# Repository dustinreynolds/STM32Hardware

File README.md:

# STM32Hardware
Repository for Kicad board development and support libraries

This repository was created on Windows using Kicad built from source using [kicad-winbuilder3.4](https://launchpad.net/kicad-winbuilder).

## Folder Hierarchy 
* Calculations - Brief calculations performed
* kicad_lib - Libraries created for new schematic or pcb objects
* Nucleo_L152RE - contains board designs that have been designed using Kicad build on 2015-05-11 from BZR commit 5650.

## Hardware Releases
So far none of the designs in this repository have been tested and verified to be working.  Footprints have been aligned with the actual components, but until the actual PCB's and the remaining components arrive, this repository should serve as a reference only.  This readme will be updated to reflect the latest testing status.

ProtoBoard Rev AA had the following issues:
	Using 5 pins from morpheo headers that didn't have a pin on them.
	RFM69HW footprint was backwards for part of it.
	See AA schematics for additional notes.

Protoboard Rev AB made the following changes:
	Removed USB, replaced with low voltage relay and fet
	Added Crypto chip ATSHA204A to i2c bus
	Added GPS to I2C bus (those same pins can be used as USART)
	Split schematic into 5 pages to ease readability
	Added 5V in and use that as main power input signal (this leaves programmer unpowered)
	Added additional voltage sense pins on 5V connector for monitoring state of battery pack
	Added 3.3V regulator that can be controlled via enable pin.  This is so SPI/I2C/OneWire devices can be powered off easily.  On board chips have low power requirements when asleep.
	Added additional spare Gnd, 3.3V, 3.3Vctl, and 5.0V lines for expansion.
	Added Servo power input for motionsense 1 and 2 (which are also pwm pins)
	Added piezo buzzer on OneWire3
	Added CS pin for RGB connector since it can be a spare SPI
	Removed mounting holes since this is securely mounted to Nucleo board.

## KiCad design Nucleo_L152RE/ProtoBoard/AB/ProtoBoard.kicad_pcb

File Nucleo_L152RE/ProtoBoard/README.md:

# STM32L152RE

The STM32 L series offers low power sleep modes that can be easily utilized to form a network of low power sensing nodes which each have the power of a 32-bit ARM Cortex M3 processor.  This board was designed to leverage these low power modes by adding high power wireless modules with low sleep currents and an on-expansion-board 128 Mb FLASH chip for offline sensor measurements.

THe STM32L152RE has 512KB of flash, 80 KB Ram and ECC backed 16KB EEPROM.  The most compelling feature was the [OpenSTM32](OpenSTM32.org) System Workbench for STM32.  Utilizing an Eclipse base IDE, Eclipse plugins are installed which give you a relatively seamless transition from writing code to debugging it.  The debugger is OpenOCD, utilizing the ST-Link. There are growing pains when transitioning to any platform, but the performance and recent availability of high quality tools make the STM32 a hot platform to start projects on. 

Development boards for a wide range of STM32 processors can be found for under $11.  Although each of those development boards only offer 64 pin packages of each respective processor, much can be done with that core subset of pins.

# Kicad Schematics and Printed Circuit Boards

## ProtoBoard
First Kicad release for the Nucleo-L152RE development board. This development board will serve as a low power platform for performing sensor measurements around my house.  Each STM32 expansion board will contain an RFM69HW wireless transceiver and will be capable of broadcasting events to the wireless network.  A listening device will then notify the owner of the event so that rapid action can occur.

### Event Detection and Alerting
The following events will be monitored
* Water leak (toilets, AC drip pan, Water Heater)
* Room temperature
* Stove burner or oven left on
* Door/window opens or closes
* Plant moisture sensing
* Dryer temperature and timing

### Firmware
The associated firmware can be found at the [SensorNodes Project](https://github.com/dustinreynolds/SensorNodes/tree/develop).  The Git-Flow paradigm is in use, so code can be found in the develop branch until a functioning first release is released, at which point it will be in the master branch (and show up by default on Github).

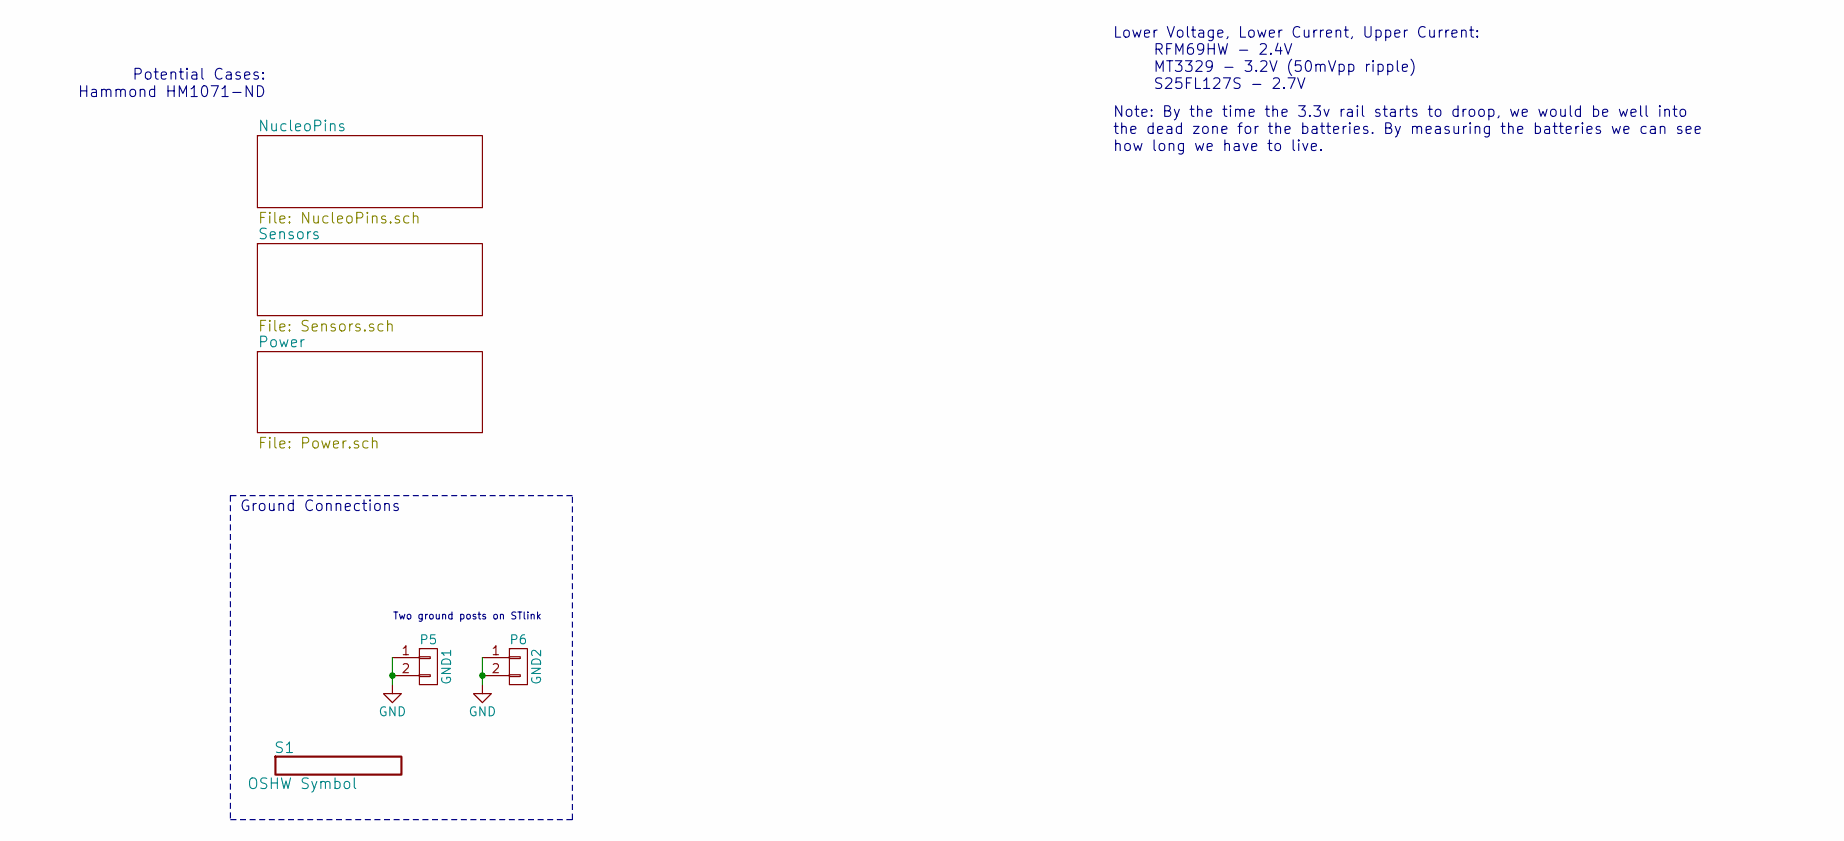
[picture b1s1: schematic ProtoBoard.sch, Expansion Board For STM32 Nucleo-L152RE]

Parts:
P5: GND1; Pin_Header_Straight_1x02
P6: GND2; Pin_Header_Straight_1x02
S1: OSHW Symbol; Symbol_OSHW-Logo_SilkScreen

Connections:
GND: P5.1, P5.2, P6.1, P6.2; also elsewhere on the board

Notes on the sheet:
Potential Cases: Hammond HM1071-ND
Ground Connections
Two ground posts on STlink
Lower Voltage, Lower Current, Upper Current: RFM69HW - 2.4V MT3329 - 3.2V (50mVpp ripple) S25FL127S - 2.7V
Note: By the time the 3.3v rail starts to droop, we would be well into the dead zone for the batteries. By measuring the batteries we can see how long we have to live.

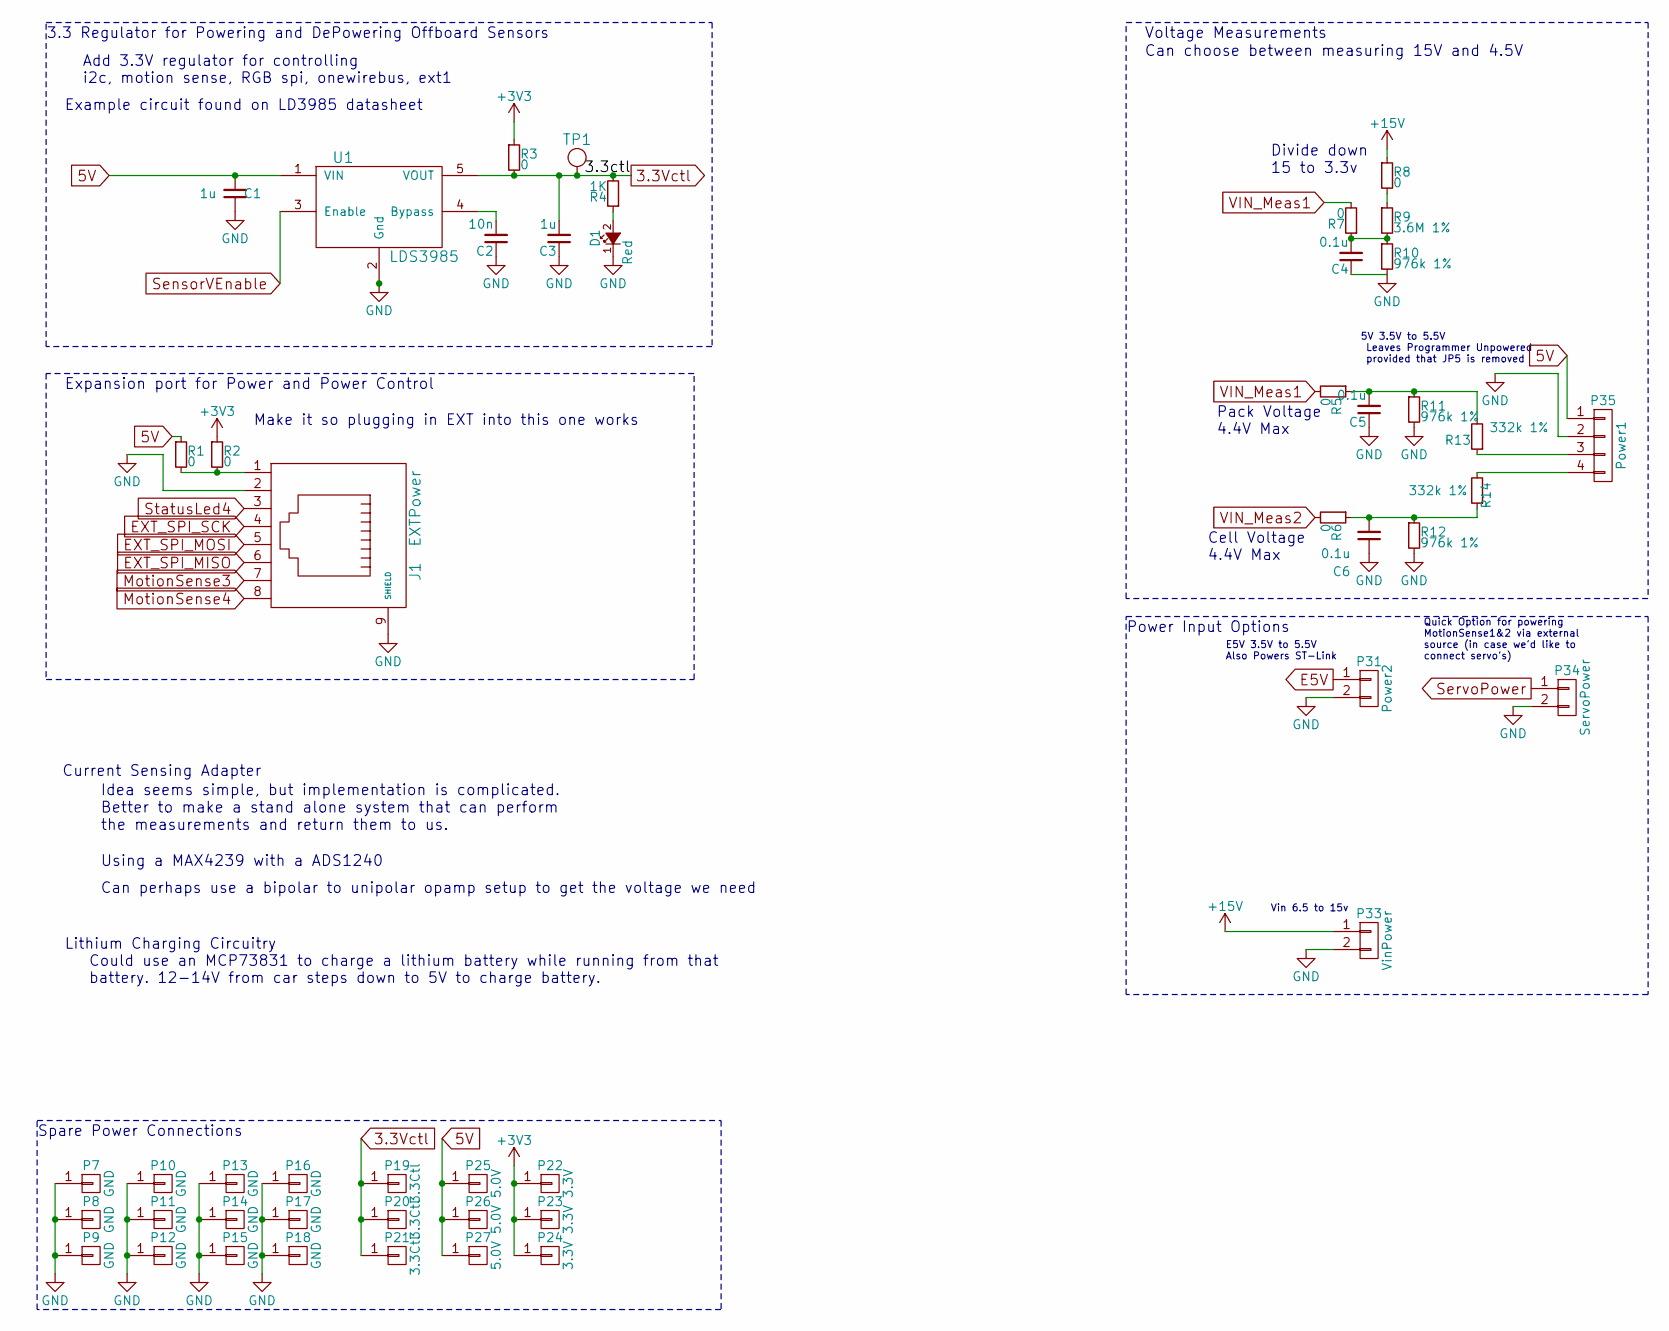
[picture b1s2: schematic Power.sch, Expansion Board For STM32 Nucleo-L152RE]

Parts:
C1, C3: 1u; C_0603_HandSoldering
C2: 10n; C_0603_HandSoldering
C4, C5, C6: 0.1u; C_0603_HandSoldering; Digikey Part Number 490-1532-1-ND
D1: Red; LED_0603_Standard; Digikey Part Number 160-1447-1-ND
J1: EXTPower; RJ45_SMD; Digikey Part Number RJLSE4238101TTR-ND
P7, P8, P9, P10, P11, P12, P13, P14, P15, P16, P17, P18: GND; Pin_Header_Straight_1x01
P19, P20, P21: 3.3Ctl; Pin_Header_Straight_1x01
P22, P23, P24: 3.3V; Pin_Header_Straight_1x01
P25, P26, P27: 5.0V; Pin_Header_Straight_1x01
P31: Power2; Pin_Header_Straight_1x02
P33: VinPower; Pin_Header_Straight_1x02
P34: ServoPower; Pin_Header_Straight_1x02
P35: Power1; Pin_Header_Straight_1x04
R1, R2, R3, R5, R6, R7, R8: 0; R_0603_HandSoldering; Digikey Part Number P0.0GCT-ND
R4: 1K; R_0603_HandSoldering; Digikey Part Number P1.0KGCT-ND
R9: 3.6M 1%; R_0603_HandSoldering
R10, R11, R12: 976k 1%; R_0603_HandSoldering
R13, R14: 332k 1%; R_0603_HandSoldering
TP1: tp; TestPoint_1mm
U1: LDS3985; SOT23-5L

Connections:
3.3Vctl: C3.2, P19.1, P20.1, P21.1, R3.2, R4.2, TP1.1, U1.5 (VOUT); also elsewhere on the board
5V: C1.2, P25.1, P26.1, P27.1, P35.1, R1.1, U1.1 (VIN); also elsewhere on the board
+3V3: P22.1, P23.1, P24.1, R2.1, R3.1; also elsewhere on the board
+15V: P33.1, R8.1; also elsewhere on the board
E5V: P31.1; also elsewhere on the board
EXT_SPI_MISO: J1.6; also elsewhere on the board
EXT_SPI_MOSI: J1.5; also elsewhere on the board
EXT_SPI_SCK: J1.4; also elsewhere on the board
GND: C1.1, C2.1, C3.1, C4.1, C5.1, C6.1, D1.1 (K), J1.2, J1.9 (SHIELD), P7.1, P8.1, P9.1, P10.1, P11.1, P12.1, P13.1, P14.1, P15.1, P16.1, P17.1, P18.1, P31.2, P33.2, P34.2, P35.2, R10.2, R11.2, R12.2, U1.2 (Gnd); also elsewhere on the board
MotionSense3: J1.7; also elsewhere on the board
MotionSense4: J1.8; also elsewhere on the board
unnamed: C2.2, U1.4 (Bypass)
unnamed: C4.2, R7.1, R9.2, R10.1
unnamed: C5.2, R5.1, R11.1, R13.2
unnamed: C6.2, R6.1, R12.1, R14.1
unnamed: D1.2 (A), R4.1
unnamed: J1.1, R1.2, R2.2
unnamed: P35.3, R13.1
unnamed: P35.4, R14.2
unnamed: R8.2, R9.1
SensorVEnable: U1.3 (Enable); also elsewhere on the board
ServoPower: P34.1; also elsewhere on the board
StatusLed4: J1.3; also elsewhere on the board
VIN_Meas1: R5.2, R7.2; also elsewhere on the board
VIN_Meas2: R6.2; also elsewhere on the board

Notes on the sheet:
Add 3.3V regulator for controlling i2c, motion sense, RGB spi, onewirebus, ext1
Voltage Measurements
Divide down 15 to 3.3v
Vin 6.5 to 15v
E5V 3.5V to 5.5V Also Powers ST-Link
Expansion port for Power and Power Control
Make it so plugging in EXT into this one works
5V 3.5V to 5.5V Leaves Programmer Unpowered provided that JP5 is removed
Cell Voltage 4.4V Max
Pack Voltage 4.4V Max
Can choose between measuring 15V and 4.5V
Current Sensing Adapter
Idea seems simple, but implementation is complicated. Better to make a stand alone system that can perform the measurements and return them to us.
Using a MAX4239 with a ADS1240
3.3 Regulator for Powering and DePowering Offboard Sensors
Power Input Options
Quick Option for powering MotionSense1&2 via external source (in case we'd like to connect servo's)
Lithium Charging Circuitry Could use an MCP73831 to charge a lithium battery while running from that battery. 12-14V from car steps down to 5V to charge battery.
Can perhaps use a bipolar to unipolar opamp setup to get the voltage we need
Spare Power Connections
Example circuit found on LD3985 datasheet

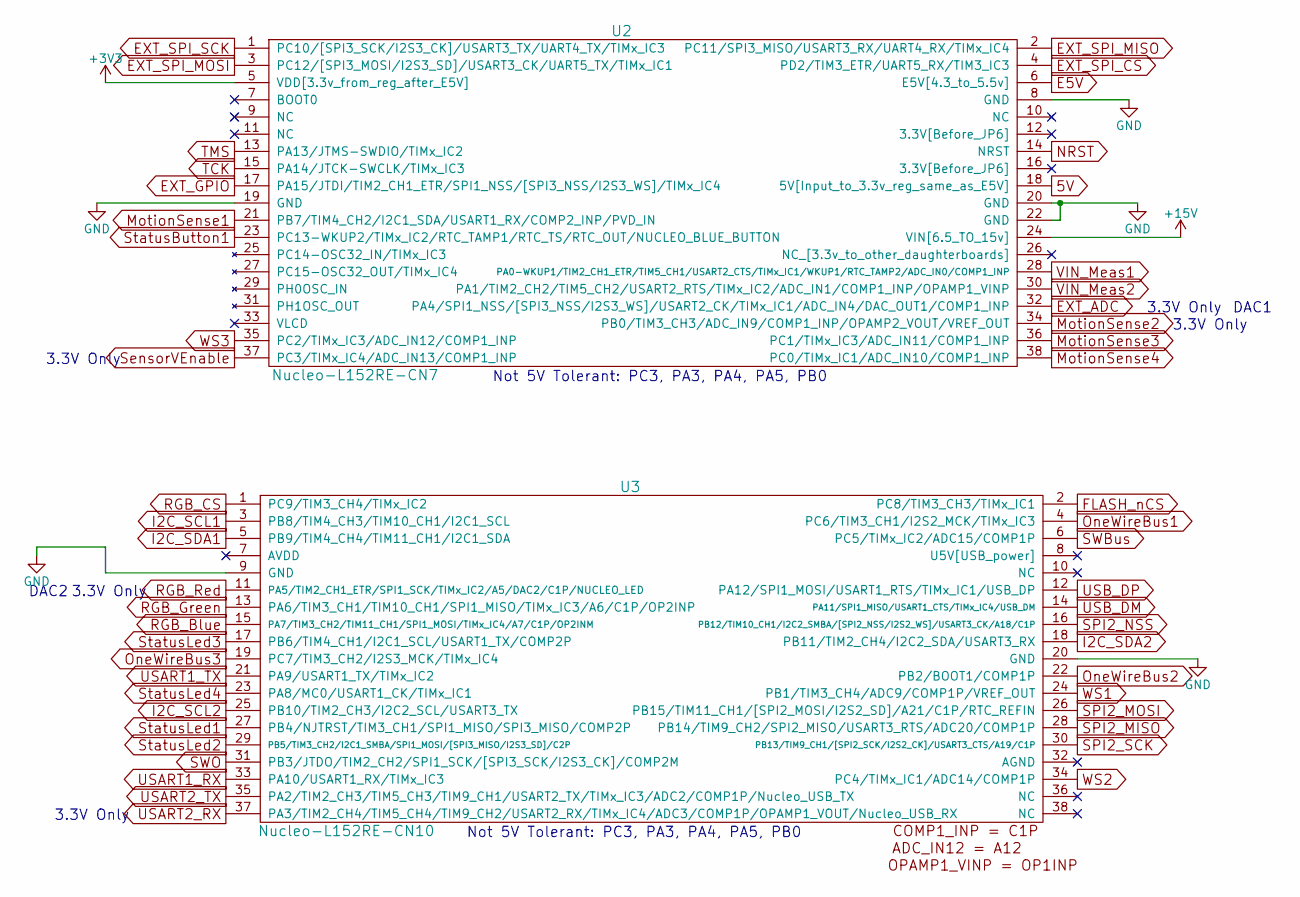
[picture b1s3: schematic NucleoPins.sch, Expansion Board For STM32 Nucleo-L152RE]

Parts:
U2: Nucleo-L152RE-CN7; Pin_Header_Straight_2x19; Digikey Part Number 497-14363-ND
U3: Nucleo-L152RE-CN10; Pin_Header_Straight_2x19

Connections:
5V: U2.18 (5V[Input_to_3.3v_reg_same_as_E5V]); also elsewhere on the board
+3V3: U2.5 (VDD[3.3v_from_reg_after_E5V]); also elsewhere on the board
+15V: U2.24 (VIN[6.5_TO_15v]); also elsewhere on the board
E5V: U2.6 (E5V[4.3_to_5.5v]); also elsewhere on the board
EXT_ADC: U2.32 (PA4/SPI1_NSS/[SPI3_NSS/I2S3_WS]/USART2_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); also elsewhere on the board
EXT_GPIO: U2.17 (PA15/JTDI/TIM2_CH1_ETR/SPI1_NSS/[SPI3_N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); also elsewhere on the board
EXT_SPI_CS: U2.4 (PD2/TIM3_ETR/UART5_RX/TIM3_IC3); also elsewhere on the board
EXT_SPI_MISO: U2.2 (PC11/SPI3_MISO/USART3_RX/UART4_RX/TIMx_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); also elsewhere on the board
EXT_SPI_MOSI: U2.3 (PC12/[SPI3_MOSI/I2S3_SD]/USART3_CK/UART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); also elsewhere on the board
EXT_SPI_SCK: U2.1 (PC10/[SPI3_SCK/I2S3_CK]/USART3_TX/UART4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); also elsewhere on the board
FLASH_nCS: U3.2 (PC8/TIM3_CH3/TIMx_IC1); also elsewhere on the board
GND: U2.8 (GND), U2.19 (GND), U2.20 (GND), U2.22 (GND), U3.9 (GND), U3.20 (GND); also elsewhere on the board
I2C_SCL1: U3.3 (PB8/TIM4_CH3/TIM10_CH1/I2C1_SCL); also elsewhere on the board
I2C_SCL2: U3.25 (PB10/TIM2_CH3/I2C2_SCL/USART3_TX); also elsewhere on the board
I2C_SDA1: U3.5 (PB9/TIM4_CH4/TIM11_CH1/I2C1_SDA); also elsewhere on the board
I2C_SDA2: U3.18 (PB11/TIM2_CH4/I2C2_SDA/USART3_RX); also elsewhere on the board
MotionSense1: U2.21 (PB7/TIM4_CH2/I2C1_SDA/USART1_RX/COMP2_I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); also elsewhere on the board
MotionSense2: U2.34 (PB0/TIM3_CH3/ADC_IN9/COMP1_INP/OPAMP2_V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); also elsewhere on the board
MotionSense3: U2.36 (PC1/TIMx_IC3/ADC_IN11/COMP1_INP); also elsewhere on the board
MotionSense4: U2.38 (PC0/TIMx_IC1/ADC_IN10/COMP1_INP); also elsewhere on the board
NRST: U2.14 (NRST); also elsewhere on the board
OneWireBus1: U3.4 (PC6/TIM3_CH1/I2S2_MCK/TIMx_IC3); also elsewhere on the board
OneWireBus2: U3.22 (PB2/BOOT1/COMP1P); also elsewhere on the board
OneWireBus3: U3.19 (PC7/TIM3_CH2/I2S3_MCK/TIMx_IC4); also elsewhere on the board
RGB_Blue: U3.15 (PA7/TIM3_CH2/TIM11_CH1/SPI1_MOSI/TIMx_I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); also elsewhere on the board
RGB_CS: U3.1 (PC9/TIM3_CH4/TIMx_IC2); also elsewhere on the board
RGB_Green: U3.13 (PA6/TIM3_CH1/TIM10_CH1/SPI1_MISO/TIMx_I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); also elsewhere on the board
RGB_Red: U3.11 (PA5/TIM2_CH1_ETR/SPI1_SCK/TIMx_IC2/A5/D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); also elsewhere on the board
SPI2_MISO: U3.28 (PB14/TIM9_CH2/SPI2_MISO/USART3_RTS/ADC2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); also elsewhere on the board
SPI2_MOSI: U3.26 (PB15/TIM11_CH1/[SPI2_MOSI/I2S2_SD]/A21/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); also elsewhere on the board
SPI2_NSS: U3.16 (PB12/TIM10_CH1/I2C2_SMBA/[SPI2_NSS/I2S2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); also elsewhere on the board
SPI2_SCK: U3.30 (PB13/TIM9_CH1/[SPI2_SCK/I2S2_CK]/USART3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); also elsewhere on the board
SWBus: U3.6 (PC5/TIMx_IC2/ADC15/COMP1P); also elsewhere on the board
SWO: U3.31 (PB3/JTDO/TIM2_CH2/SPI1_SCK/[SPI3_SCK/I2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); also elsewhere on the board
SensorVEnable: U2.37 (PC3/TIMx_IC4/ADC_IN13/COMP1_INP); also elsewhere on the board
StatusButton1: U2.23 (PC13-WKUP2/TIMx_IC2/RTC_TAMP1/RTC_TS/RT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); also elsewhere on the board
StatusLed1: U3.27 (PB4/NJTRST/TIM3_CH1/SPI1_MISO/SPI3_MISO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); also elsewhere on the board
StatusLed2: U3.29 (PB5/TIM3_CH2/I2C1_SMBA/SPI1_MOSI/[SPI3_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); also elsewhere on the board
StatusLed3: U3.17 (PB6/TIM4_CH1/I2C1_SCL/USART1_TX/COMP2P); also elsewhere on the board
StatusLed4: U3.23 (PA8/MC0/USART1_CK/TIMx_IC1); also elsewhere on the board
TCK: U2.15 (PA14/JTCK-SWCLK/TIMx_IC3); also elsewhere on the board
TMS: U2.13 (PA13/JTMS-SWDIO/TIMx_IC2); also elsewhere on the board
USART1_RX: U3.33 (PA10/USART1_RX/TIMx_IC3); also elsewhere on the board
USART1_TX: U3.21 (PA9/USART1_TX/TIMx_IC2); also elsewhere on the board
USART2_RX: U3.37 (PA3/TIM2_CH4/TIM5_CH4/TIM9_CH2/USART2_R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); also elsewhere on the board
USART2_TX: U3.35 (PA2/TIM2_CH3/TIM5_CH3/TIM9_CH1/USART2_T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); also elsewhere on the board
USB_DM: U3.14 (PA11/SPI1_MISO/USART1_CTS/TIMx_IC4/USB_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); also elsewhere on the board
USB_DP: U3.12 (PA12/SPI1_MOSI/USART1_RTS/TIMx_IC1/USB_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); also elsewhere on the board
VIN_Meas1: U2.28 (PA0-WKUP1/TIM2_CH1_ETR/TIM5_CH1/USART2_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); also elsewhere on the board
VIN_Meas2: U2.30 (PA1/TIM2_CH2/TIM5_CH2/USART2_RTS/TIMx_I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); also elsewhere on the board
WS1: U3.24 (PB1/TIM3_CH4/ADC9/COMP1P/VREF_OUT); also elsewhere on the board
WS2: U3.34 (PC4/TIMx_IC1/ADC14/COMP1P); also elsewhere on the board
WS3: U2.35 (PC2/TIMx_IC3/ADC_IN12/COMP1_INP); also elsewhere on the board

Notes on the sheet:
Not 5V Tolerant: PC3, PA3, PA4, PA5, PB0
DAC2
DAC1
3.3V Only

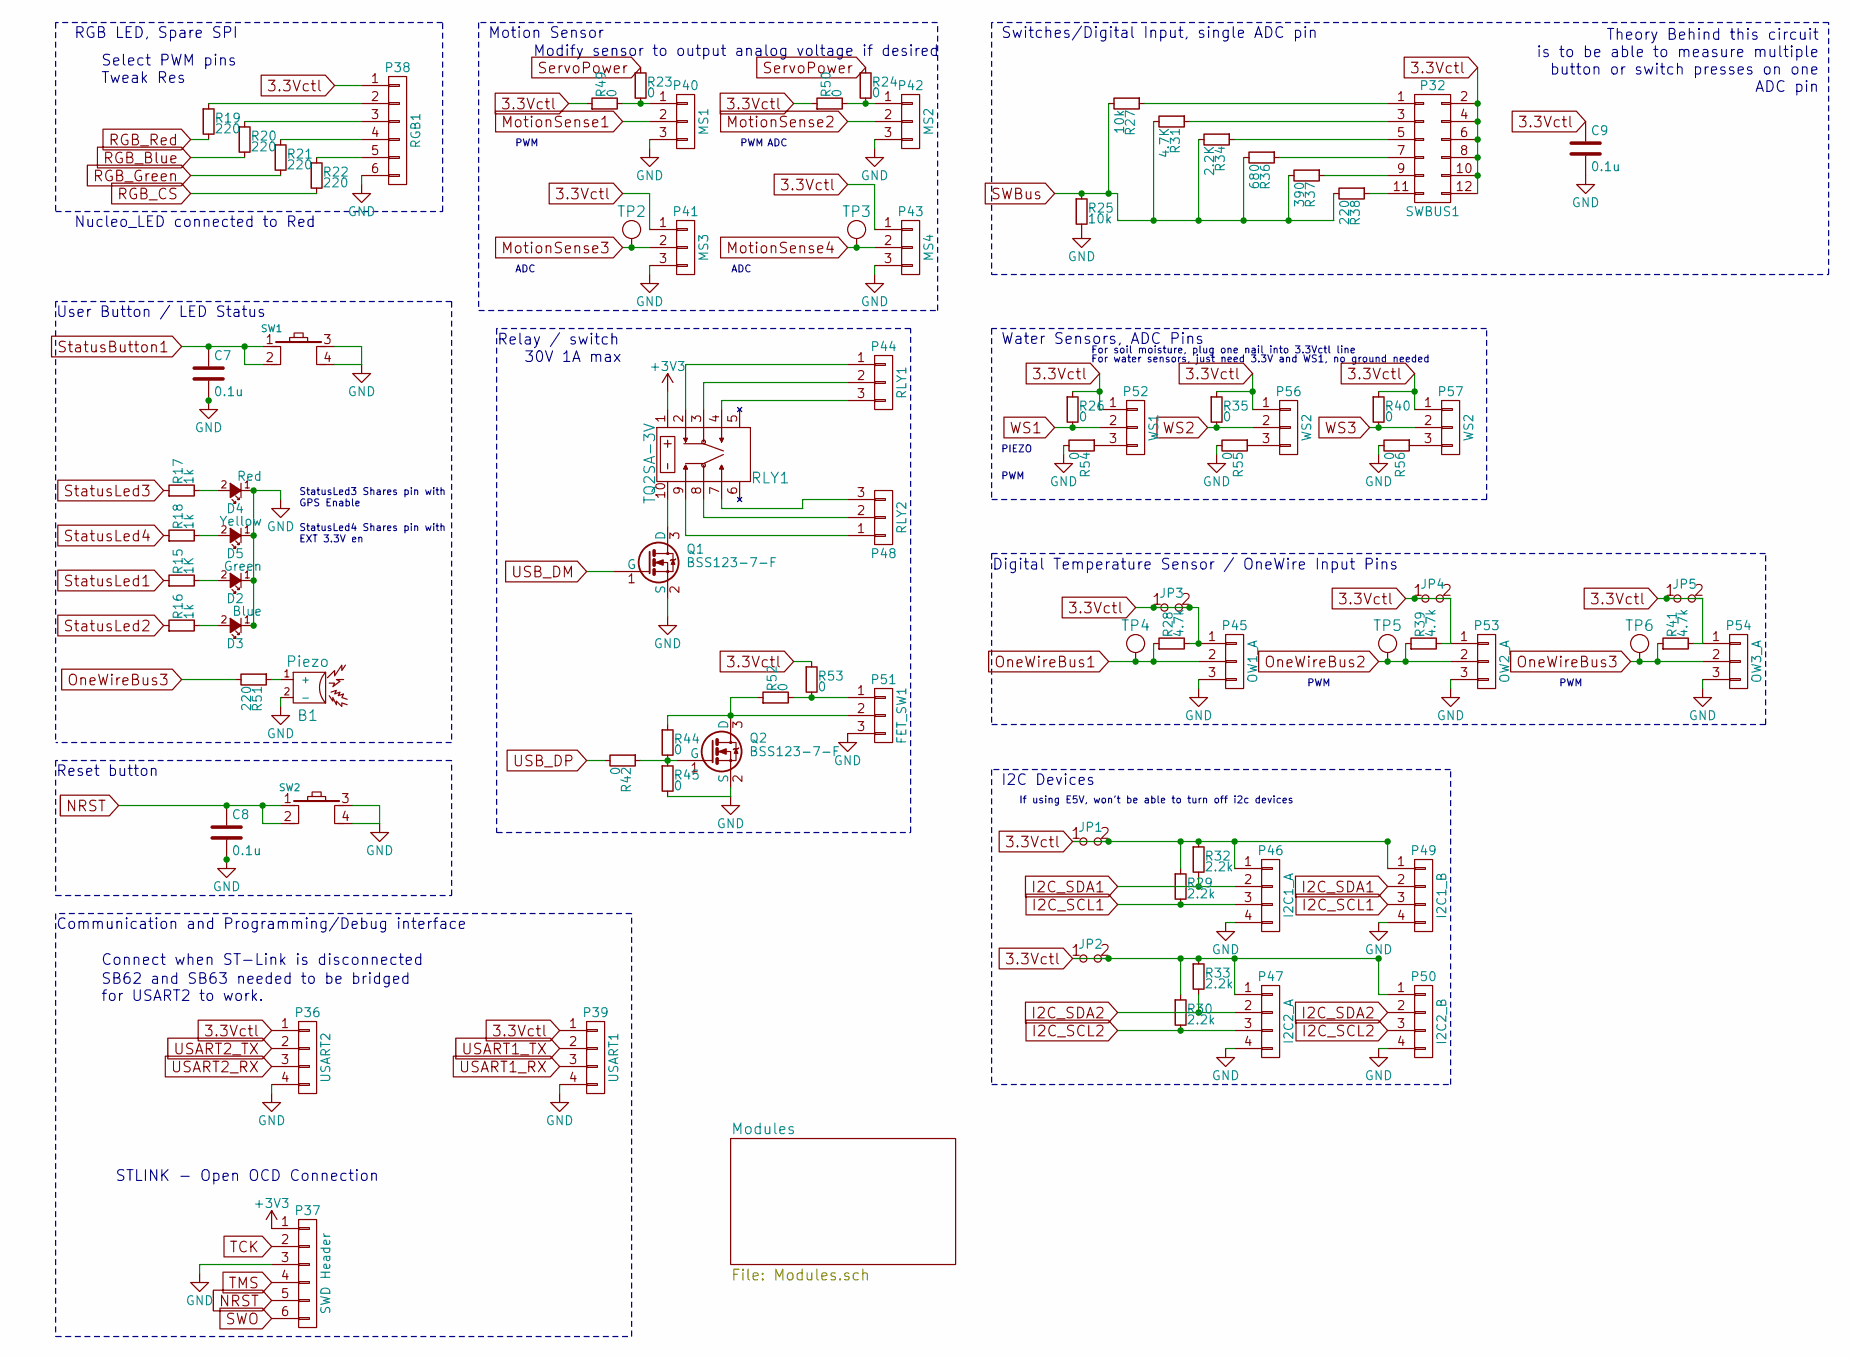
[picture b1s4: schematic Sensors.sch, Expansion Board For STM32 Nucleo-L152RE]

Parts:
B1: Piezo; Piezo_12mm
C7, C8, C9: 0.1u; C_0603; Digikey Part Number 490-1532-1-ND
D2: Green; LED_0603_Standard; Digikey Part Number 160-1446-1-ND
D3: Blue; LED_0603_Standard; Digikey Part Number 160-1647-1-ND
D4: Red; LED_0603_Standard; Digikey Part Number 160-1447-1-ND
D5: Yellow; LED_0603_Standard; Digikey Part Number 160-1448-1-ND
JP1, JP2, JP3, JP4, JP5: Jumper_NC_Small; SB_NO_Smaller
P32: SWBUS1; Pin_Header_Straight_2x06
P36: USART2; Pin_Header_Straight_1x04
P37: SWD Header; Pin_Header_Straight_1x06
P38: RGB1; Pin_Header_Straight_1x06
P39: USART1; Pin_Header_Straight_1x04
P40: MS1; Pin_Header_Straight_1x03
P41: MS3; Pin_Header_Straight_1x03
P42: MS2; Pin_Header_Straight_1x03
P43: MS4; Pin_Header_Straight_1x03
P44: RLY1; Pin_Header_Straight_1x03
P45: OW1_A; Pin_Header_Straight_1x03
P46: I2C1_A; Pin_Header_Straight_1x04
P47: I2C2_A; Pin_Header_Straight_1x04
P48: RLY2; Pin_Header_Straight_1x03
P49: I2C1_B; Pin_Header_Straight_1x04
P50: I2C2_B; Pin_Header_Straight_1x04
P51: FET_SW1; Pin_Header_Straight_1x03
P52: WS1; Pin_Header_Straight_1x03
P53: OW2_A; Pin_Header_Straight_1x03
P54: OW3_A; Pin_Header_Straight_1x03
P56, P57: WS2; Pin_Header_Straight_1x03
Q1, Q2: BSS123-7-F; SOT23-3
R15: 1K; R_0603_HandSoldering; Digikey Part Number P1.0KGCT-ND
R16, R17, R18: 1k; R_0603_HandSoldering; Digikey Part Number P1.0KGCT-ND
R19, R20, R21, R22, R38, R51: 220; R_0603_HandSoldering; Digikey Part Number P220GCT-ND
R23, R24, R26, R35, R40, R42, R44, R45, R49, R50, R52, R53, R54, R55, R56: 0; R_0603_HandSoldering; Digikey Part Number P0.0GCT-ND
R25, R27: 10k; R_0603_HandSoldering; Digikey Part Number P10KGCT-ND
R28, R39, R41: 4.7k; R_0603_HandSoldering; Digikey Part Number P4.7KGCT-ND
R29, R30, R32, R33: 2.2k; R_0603_HandSoldering; Digikey Part Number P2.2KGCT-ND
R31: 4.7K; R_0603_HandSoldering; Digikey Part Number P4.7KGCT-ND
R34: 2.2K; R_0603_HandSoldering; Digikey Part Number P2.2KGCT-ND
R36: 680; R_0603_HandSoldering; Digikey Part Number P680GCT-ND
R37: 390; R_0603_HandSoldering; Digikey Part Number P390GCT-ND
RLY1: TQ2SA-3V; Relay_SMD
SW1: MomentarySwitch; Tact_switch; Digikey Part Number 450-1650-ND
SW2: ResetSwitch; Tact_switch; Digikey Part Number 450-1650-ND
TP2, TP3, TP4, TP5, TP6: tp; TestPoint_1mm

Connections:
3.3Vctl: C9.1, JP1.1, JP1.2, JP2.1, JP2.2, JP3.1, JP3.2, JP4.1, JP4.2, JP5.1, JP5.2, P32.2, P32.4, P32.6, P32.8, P32.10, P32.12, P36.1, P38.1, P39.1, P41.1, P43.1, P45.1, P46.1, P47.1, P49.1, P50.1, P52.1, P53.1, P54.1, P56.1, P57.1, R26.1, R28.2, R29.1, R30.1, R32.1, R33.1, R35.1, R39.2, R40.1, R41.2, R49.1, R50.1, R53.1; also elsewhere on the board
+3V3: P37.1, RLY1.1; also elsewhere on the board
GND: B1.2 (-), C7.2, C8.2, C9.2, D2.1 (K), D3.1 (K), D4.1 (K), D5.1 (K), P36.4, P37.3, P38.6, P39.4, P40.3, P41.3, P42.3, P43.3, P45.3, P46.4, P47.4, P49.4, P50.4, P51.3, P53.3, P54.3, Q1.2 (S), Q2.2 (S), R25.2, R45.2, R54.2, R55.2, R56.2, SW1.3, SW1.4, SW2.3, SW2.4; also elsewhere on the board
I2C_SCL1: P46.3, P49.3, R29.2; also elsewhere on the board
I2C_SCL2: P47.3, P50.3, R30.2; also elsewhere on the board
I2C_SDA1: P46.2, P49.2, R32.2; also elsewhere on the board
I2C_SDA2: P47.2, P50.2, R33.2; also elsewhere on the board
MotionSense1: P40.2; also elsewhere on the board
MotionSense2: P42.2; also elsewhere on the board
MotionSense3: P41.2, TP2.1; also elsewhere on the board
MotionSense4: P43.2, TP3.1; also elsewhere on the board
NRST: C8.1, P37.5, SW2.1, SW2.2; also elsewhere on the board
unnamed: B1.1 (+), R51.1
unnamed: D2.2 (A), R15.2
unnamed: D3.2 (A), R16.2
unnamed: D4.2 (A), R17.2
unnamed: D5.2 (A), R18.2
unnamed: P32.1, R27.1
unnamed: P32.3, R31.1
unnamed: P32.5, R34.1
unnamed: P32.7, R36.1
unnamed: P32.9, R37.1
unnamed: P32.11, R38.1
unnamed: P38.2, R19.1
unnamed: P38.3, R20.1
unnamed: P38.4, R21.1
unnamed: P38.5, R22.1
unnamed: P40.1, R23.2, R49.2
unnamed: P42.1, R24.2, R50.2
unnamed: P44.1, RLY1.2
unnamed: P44.2, RLY1.3
unnamed: P44.3, RLY1.4
unnamed: P48.1, RLY1.9
unnamed: P48.2, RLY1.8
unnamed: P48.3, RLY1.7
unnamed: P51.1, R52.2, R53.2
unnamed: P51.2, Q2.3 (D), R44.1, R52.1
unnamed: P52.3, R54.1
unnamed: P56.3, R55.1
unnamed: P57.3, R56.1
unnamed: Q1.3 (D), RLY1.10
unnamed: Q2.1 (G), R42.1, R44.2, R45.1
OneWireBus1: P45.2, R28.1, TP4.1; also elsewhere on the board
OneWireBus2: P53.2, R39.1, TP5.1; also elsewhere on the board
OneWireBus3: P54.2, R41.1, R51.2, TP6.1; also elsewhere on the board
RGB_Blue: R20.2; also elsewhere on the board
RGB_CS: R22.2; also elsewhere on the board
RGB_Green: R21.2; also elsewhere on the board
RGB_Red: R19.2; also elsewhere on the board
SWBus: R25.1, R27.2, R31.2, R34.2, R36.2, R37.2, R38.2; also elsewhere on the board
SWO: P37.6; also elsewhere on the board
ServoPower: R23.1, R24.1; also elsewhere on the board
StatusButton1: C7.1, SW1.1, SW1.2; also elsewhere on the board
StatusLed1: R15.1; also elsewhere on the board
StatusLed2: R16.1; also elsewhere on the board
StatusLed3: R17.1; also elsewhere on the board
StatusLed4: R18.1; also elsewhere on the board
TCK: P37.2; also elsewhere on the board
TMS: P37.4; also elsewhere on the board
USART1_RX: P39.3; also elsewhere on the board
USART1_TX: P39.2; also elsewhere on the board
USART2_RX: P36.3; also elsewhere on the board
USART2_TX: P36.2; also elsewhere on the board
USB_DM: Q1.1 (G); also elsewhere on the board
USB_DP: R42.2; also elsewhere on the board
WS1: P52.2, R26.2; also elsewhere on the board
WS2: P56.2, R35.2; also elsewhere on the board
WS3: P57.2, R40.2; also elsewhere on the board

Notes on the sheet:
Switches/Digital Input, single ADC pin
Water Sensors, ADC Pins
Digital Temperature Sensor / OneWire Input Pins
Motion Sensor
Theory Behind this circuit is to be able to measure multiple button or switch presses on one ADC pin
If using E5V, won't be able to turn off i2c devices
RGB LED, Spare SPI
Select PWM pins Tweak Res
I2C Devices
PWM
StatusLed3 Shares pin with GPS Enable
StatusLed4 Shares pin with EXT 3.3V en
Modify sensor to output analog voltage if desired
Connect when ST-Link is disconnected
STLINK - Open OCD Connection
SB62 and SB63 needed to be bridged for USART2 to work.
Communication and Programming/Debug interface
User Button / LED Status
Reset button
PIEZO
ADC
For soil moisture, plug one nail into 3.3Vctl line
For water sensors, just need 3.3V and WS1, no ground needed
Relay / switch
Nucleo_LED connected to Red
30V 1A max

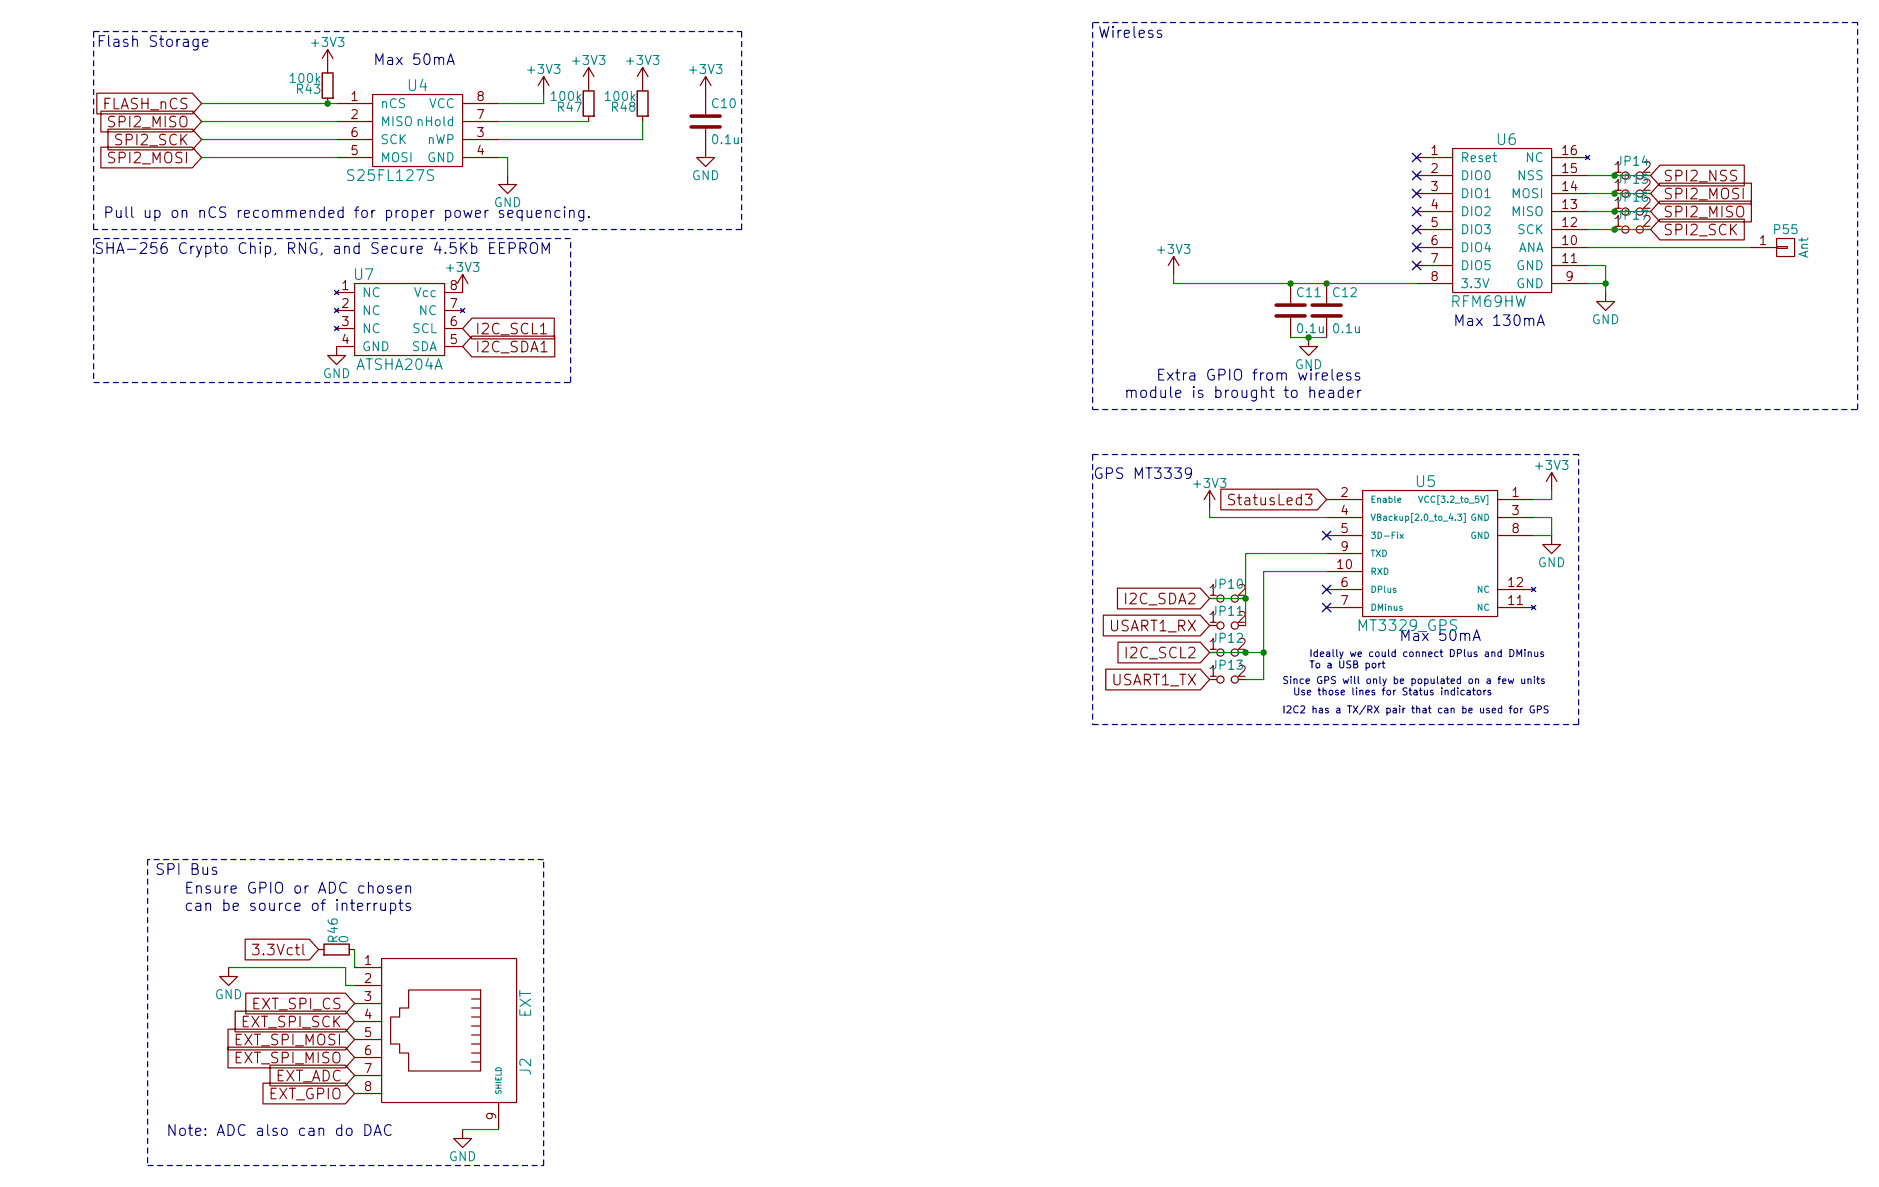
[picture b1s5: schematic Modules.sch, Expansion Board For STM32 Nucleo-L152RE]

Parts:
C10, C11, C12: 0.1u; C_0603; Digikey Part Number 490-1532-1-ND
J2: EXT; RJ45_SMD; Digikey Part Number RJLSE4238101TTR-ND
JP10, JP12, JP14, JP15, JP16, JP17: Jumper_NC_Small; SB_NO_Smaller
JP11, JP13: Jumper_NO_Small; SB_NO_Smaller
P55: Ant; Antenna_1pin
R43, R47, R48: 100k; R_0603_HandSoldering; Digikey Part Number RMCF0603FT100KTR-ND
R46: 0; R_0603_HandSoldering; Digikey Part Number P0.0GCT-ND
U4: S25FL127S; SOIC-8-FLASH; Digikey Part Number 1274-1045-ND
U5: MT3329_GPS; MT3329_LessPins
U6: RFM69HW; RFM69HW_LessPins
U7: ATSHA204A; 8-SOIC-JEDEC_MS-012AA

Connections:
3.3Vctl: R46.1; also elsewhere on the board
+3V3: C10.1, C11.1, C12.1, R43.2, R47.2, R48.2, U4.8 (VCC), U5.1 (VCC[3.2_to_5V]), U5.4 (VBackup[2.0_to_4.3]), U6.8 (3.3V), U7.8 (Vcc); also elsewhere on the board
EXT_ADC: J2.7; also elsewhere on the board
EXT_GPIO: J2.8; also elsewhere on the board
EXT_SPI_CS: J2.3; also elsewhere on the board
EXT_SPI_MISO: J2.6; also elsewhere on the board
EXT_SPI_MOSI: J2.5; also elsewhere on the board
EXT_SPI_SCK: J2.4; also elsewhere on the board
FLASH_nCS: R43.1, U4.1 (nCS); also elsewhere on the board
GND: C10.2, C11.2, C12.2, J2.2, J2.9 (SHIELD), U4.4 (GND), U5.3 (GND), U5.8 (GND), U6.9 (GND), U6.11 (GND), U7.4 (GND); also elsewhere on the board
I2C_SCL1: U7.6 (SCL); also elsewhere on the board
I2C_SCL2: JP12.1, JP12.2, JP13.2, U5.10 (RXD); also elsewhere on the board
I2C_SDA1: U7.5 (SDA); also elsewhere on the board
I2C_SDA2: JP10.1, JP10.2, JP11.2, U5.9 (TXD); also elsewhere on the board
unnamed: J2.1, R46.2
unnamed: P55.1, U6.10 (ANA)
unnamed: R47.1, U4.7 (nHold)
unnamed: R48.1, U4.3 (nWP)
SPI2_MISO: JP16.1, JP16.2, U4.2 (MISO), U6.13 (MISO); also elsewhere on the board
SPI2_MOSI: JP15.1, JP15.2, U4.5 (MOSI), U6.14 (MOSI); also elsewhere on the board
SPI2_NSS: JP14.1, JP14.2, U6.15 (NSS); also elsewhere on the board
SPI2_SCK: JP17.1, JP17.2, U4.6 (SCK), U6.12 (SCK); also elsewhere on the board
StatusLed3: U5.2 (Enable); also elsewhere on the board
USART1_RX: JP11.1; also elsewhere on the board
USART1_TX: JP13.1; also elsewhere on the board

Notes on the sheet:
Flash Storage
Max 50mA
Wireless
Extra GPIO from wireless module is brought to header
Max 130mA
SPI Bus
Ensure GPIO or ADC chosen can be source of interrupts
Note: ADC also can do DAC
Ideally we could connect DPlus and DMinus To a USB port
GPS MT3339
Since GPS will only be populated on a few units Use those lines for Status indicators
I2C2 has a TX/RX pair that can be used for GPS
Pull up on nCS recommended for proper power sequencing.
SHA-256 Crypto Chip, RNG, and Secure 4.5Kb EEPROM

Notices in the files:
Nucleo_L152RE/ProtoBoard/AA/ProtoBoard.kicad_pcb:
Creative Commons - Share Alike
Nucleo_L152RE/ProtoBoard/AB/Modules.sch:
MIT License
